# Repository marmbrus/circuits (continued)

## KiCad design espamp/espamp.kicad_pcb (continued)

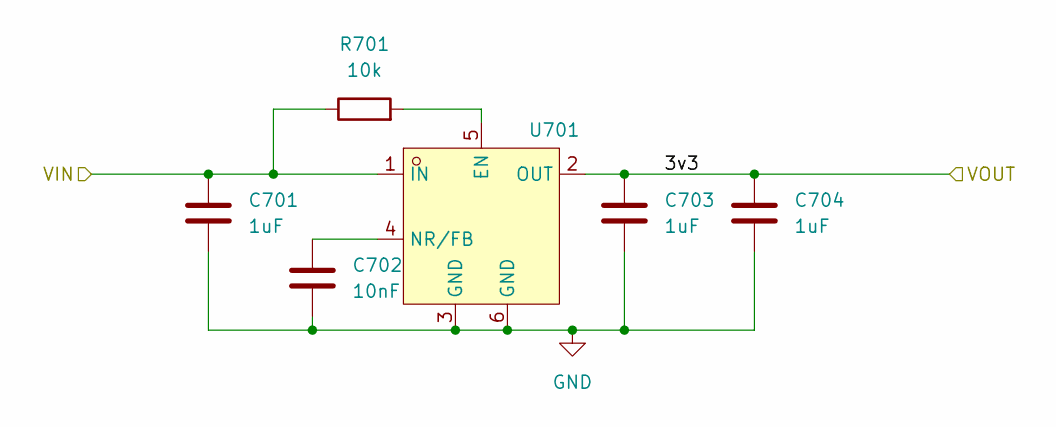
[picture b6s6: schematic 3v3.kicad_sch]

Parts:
C701, C703, C704: 1uF; C_0603_1608Metric
C702: 10nF; C_0603_1608Metric
R701: 10k; R_0603_1608Metric
U701: TPS73733DCQ_C5220270; SOT-223-6_L6.5-W3.5-P1.27-LS7.0-BR; LCSC Part C5220270

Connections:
/3v3/3v3: C703.1, C704.1, U701.2 (OUT); also elsewhere on the board
/5V: C701.1, R701.1, U701.1 (IN); also elsewhere on the board
GND: C701.2, C702.2, C703.2, C704.2, U701.3 (GND), U701.6 (GND); also elsewhere on the board
unnamed: R701.2, U701.5 (EN)
unnamed: C702.1, U701.4 (NR/FB)

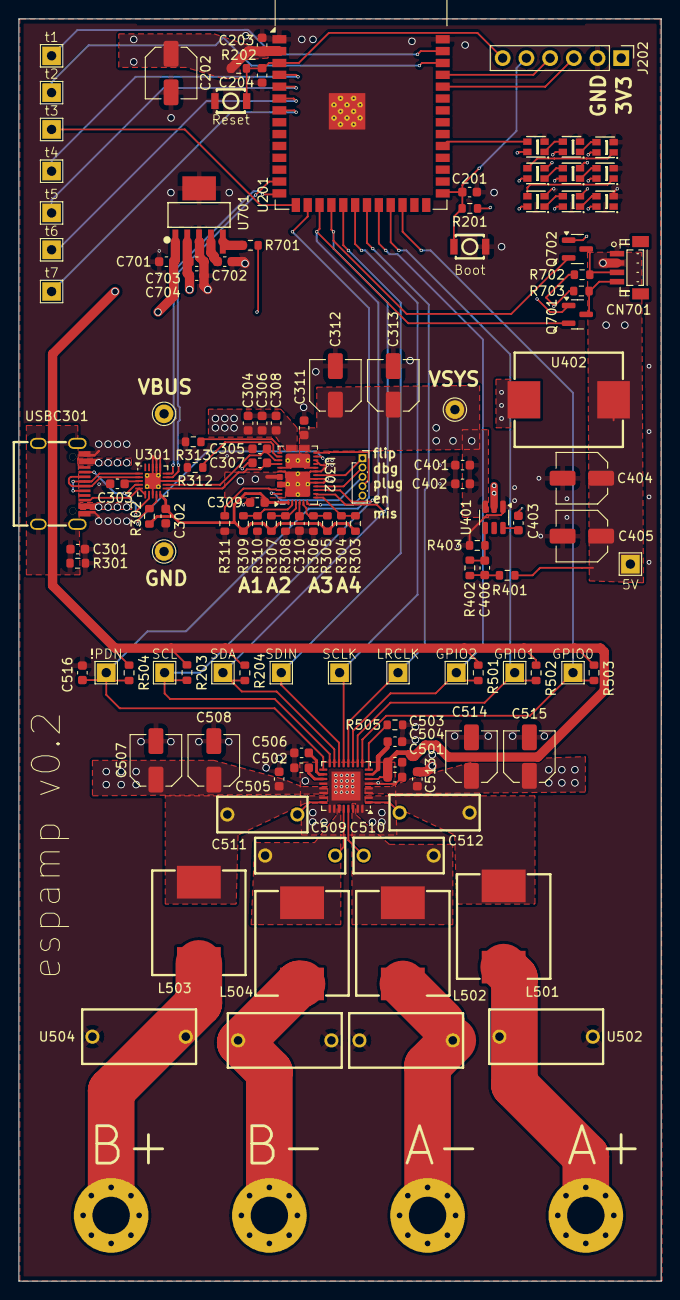
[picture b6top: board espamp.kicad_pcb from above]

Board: 4 copper layers, 68.8 x 135.2 mm, 127 parts (0 on the bottom side), 84 nets.

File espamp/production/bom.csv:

Designator,Footprint,Quantity,Value,LCSC Part #
"C201, C302, C502, C503, C506, C516, C701, C703, C704",0603,9,1uf,
"C202, C312, C313, C404, C405, C507, C508, C514, C515",C_Elec_5x5.8,9,22uF,C336246
"C203, C301, C303, C306, C402, C403, C504, C505, C513",0603,9,100nF,
"C204, C309, C311, C401",0603,4,10uf,
"C304, C310, C501",0603,3,4.7uF,
"C305, C307",0603,2,330pF,
"C308, C702",0603,2,10nF,
C406,0603,1,75pF,
"C509, C510, C511, C512",CAP-TH_L9.5-W3.7-P7.50-D0.5,4,MPP474J2A0701,C3019096
CN701,CONN-SMD_BM04B-SRSS-TB,1,BM04B-SRSS-TB(LF)(SN),C160390
"L501, L502, L503, L504",IND-SMD_L11.0-W10.2,4,SL1040-100M,C22463839
"LED201, LED202, LED203, LED204, LED205, LED206, LED207, LED208, LED209",LED-SMD_4P-L2.0-W2.0-TL_WS2812B-2020,9,WS2812B-2020,C965555
"Q701, Q702",SOT-23,2,BSS138,
"R201, R202, R203, R204, R302, R311, R312, R313, R501, R502, R503, R504, R701, R702, R703",0603,15,10k,
R301,0603,1,1M,
R303,0603,1,162k,
R304,0603,1,37.4,
"R305, R308",0603,2,191k,
"R306, R307",0603,2,9.31k,
R309,0603,1,196k,
R310,0603,1,2.2k,
R401,0603,1,49.9,
R402,0603,1,100k,
R403,0603,1,13.3k,
R505,0603,1,0,
"SW201, SW202",KEY-SMD_B3U-1000PM,2,KEY-SMD_B3U-1000PM,C231329
U201,ESP32-S3-WROOM-1,1,ESP32-S3-WROOM-1,
U301,WQFN-20-1EP_3x3mm_P0.4mm_EP1.7x1.7mm_ThermalVias,1,TPD6S300A,
U302,Texas_REF0038A_WQFN-38-2EP_6x4mm_P0.4,1,TPS25730D,
U401,SOT-23-6,1,TPS54202DDC,
U402,IND-SMD_L11.6-W10.1,1,CYA1040-15UH,C6364678
U501,VQFN-32-1EP_5x5mm_P0.5mm_EP3.1x3.1mm,1,TAS5825MRHB,
"U502, U503, U504, U505",CAP-TH_L12.0-W5.8-P10.00-D0.6,4,MPP684J2S1001,C3019017
U701,SOT-223-6_L6.5-W3.5-P1.27-LS7.0-BR,1,TPS73733DCQ_C5220270,C5220270
USBC301,USB-C_SMD-TYPE-C-31-M-12,1,TYPE-C-31-M-12,C165948

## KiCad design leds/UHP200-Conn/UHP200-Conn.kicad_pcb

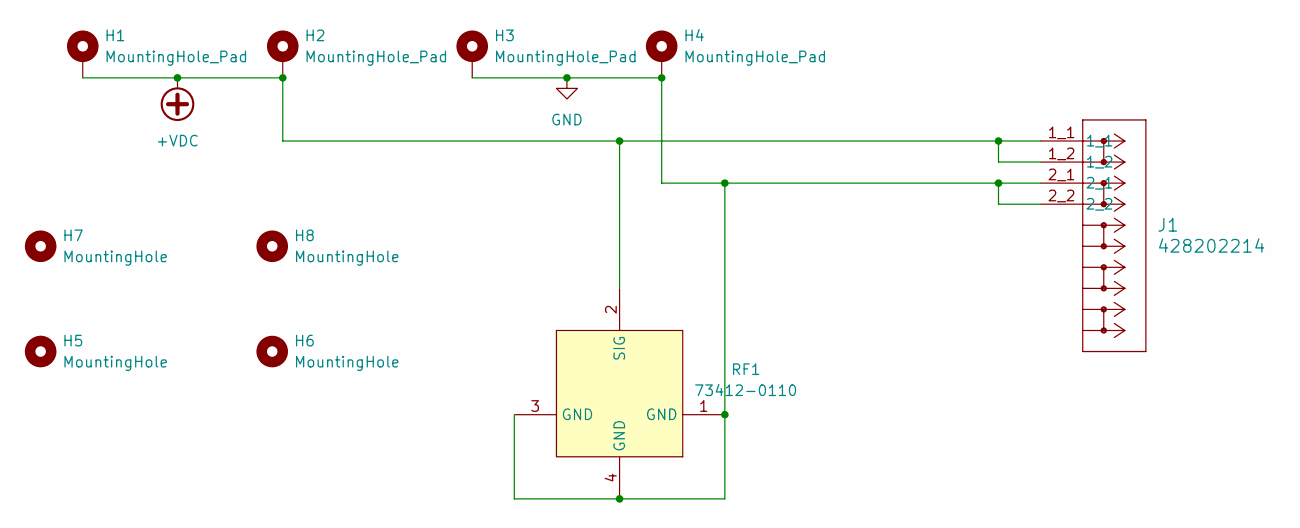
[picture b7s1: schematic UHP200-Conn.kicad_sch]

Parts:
H1, H2, H3, H4: MountingHole_Pad; MountingHole_3.5mm_Pad_Via
H5, H6, H8: MountingHole; MountingHole_3.7mm
H7: MountingHole; MountingHole_3.5mm
J1: 428202214; CONN_SDA-42820-0002_02_RC_MOL
RF1: 73412-0110; ANT-SMD_73412-0110; LCSC Part C434806

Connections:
+VDC: H1.1, H2.1, J1.1_1, J1.1_2, RF1.2 (SIG)
GND: H3.1, H4.1, J1.2_1, J1.2_2, RF1.1 (GND), RF1.3 (GND), RF1.4 (GND)

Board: 2 copper layers, 10 parts (0 on the bottom side), 2 nets, no tracks yet.

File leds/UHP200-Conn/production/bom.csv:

Designator,Footprint,Quantity,Value,LCSC Part #
J1,CONN_SDA-42820-0002_02_RC_MOL,1,428202214,
RF1,ANT-SMD_73412-0110,1,73412-0110,C434806
